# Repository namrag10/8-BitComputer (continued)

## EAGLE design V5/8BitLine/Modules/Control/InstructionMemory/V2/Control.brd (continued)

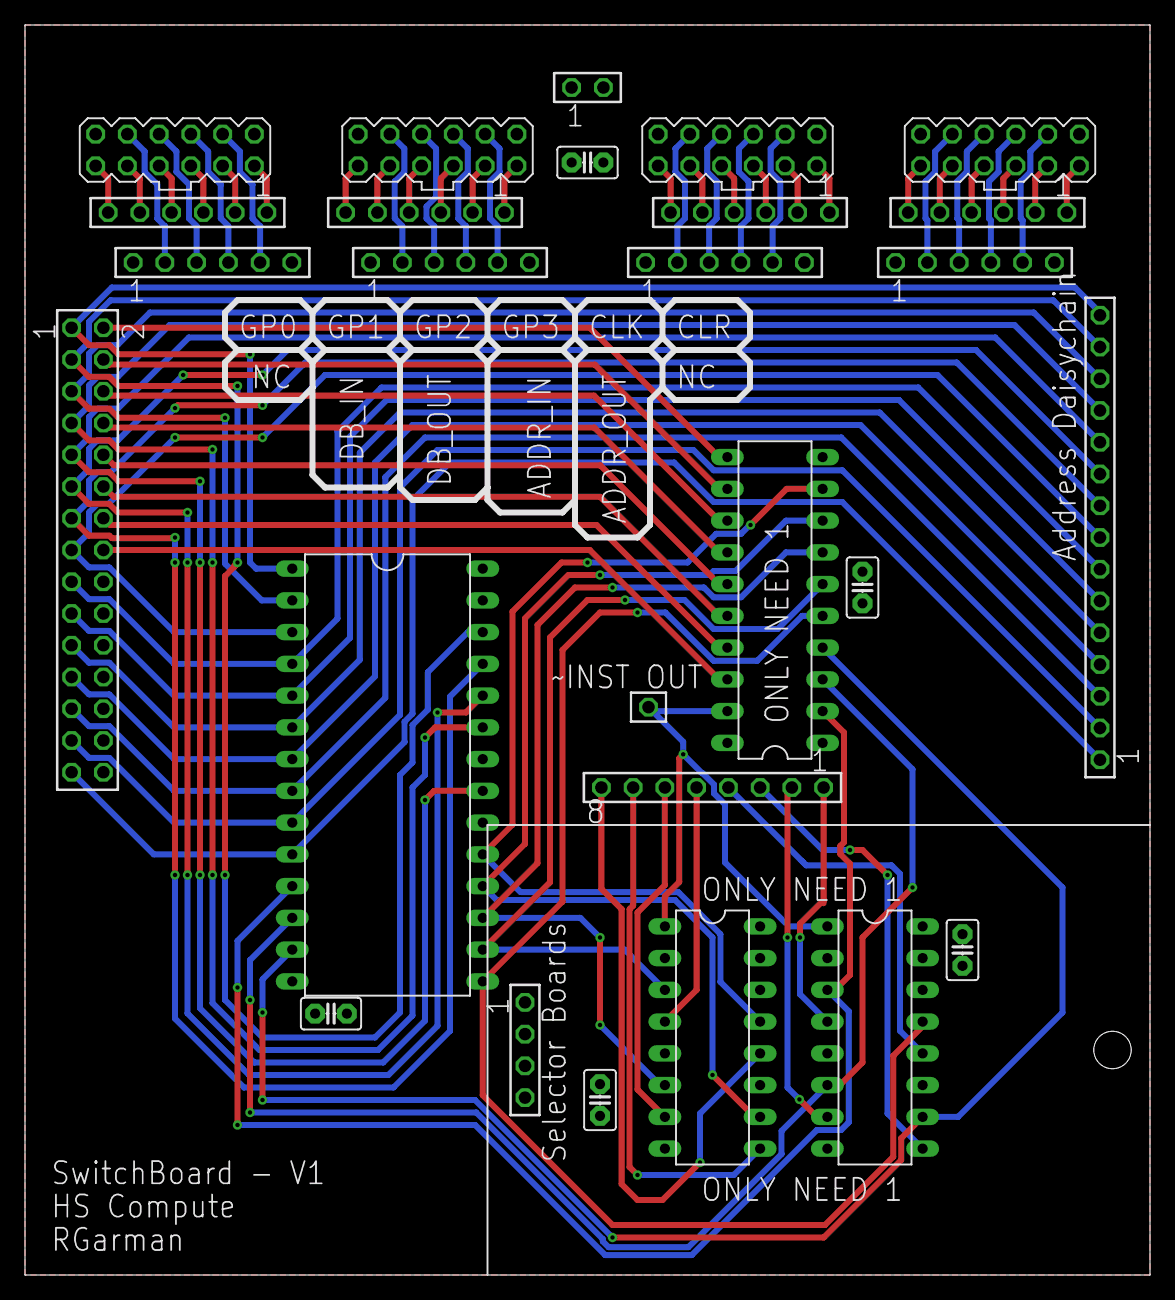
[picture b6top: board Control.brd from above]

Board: 2 copper layers, 90.0 x 100.0 mm, 27 parts (0 on the bottom side), 82 nets.

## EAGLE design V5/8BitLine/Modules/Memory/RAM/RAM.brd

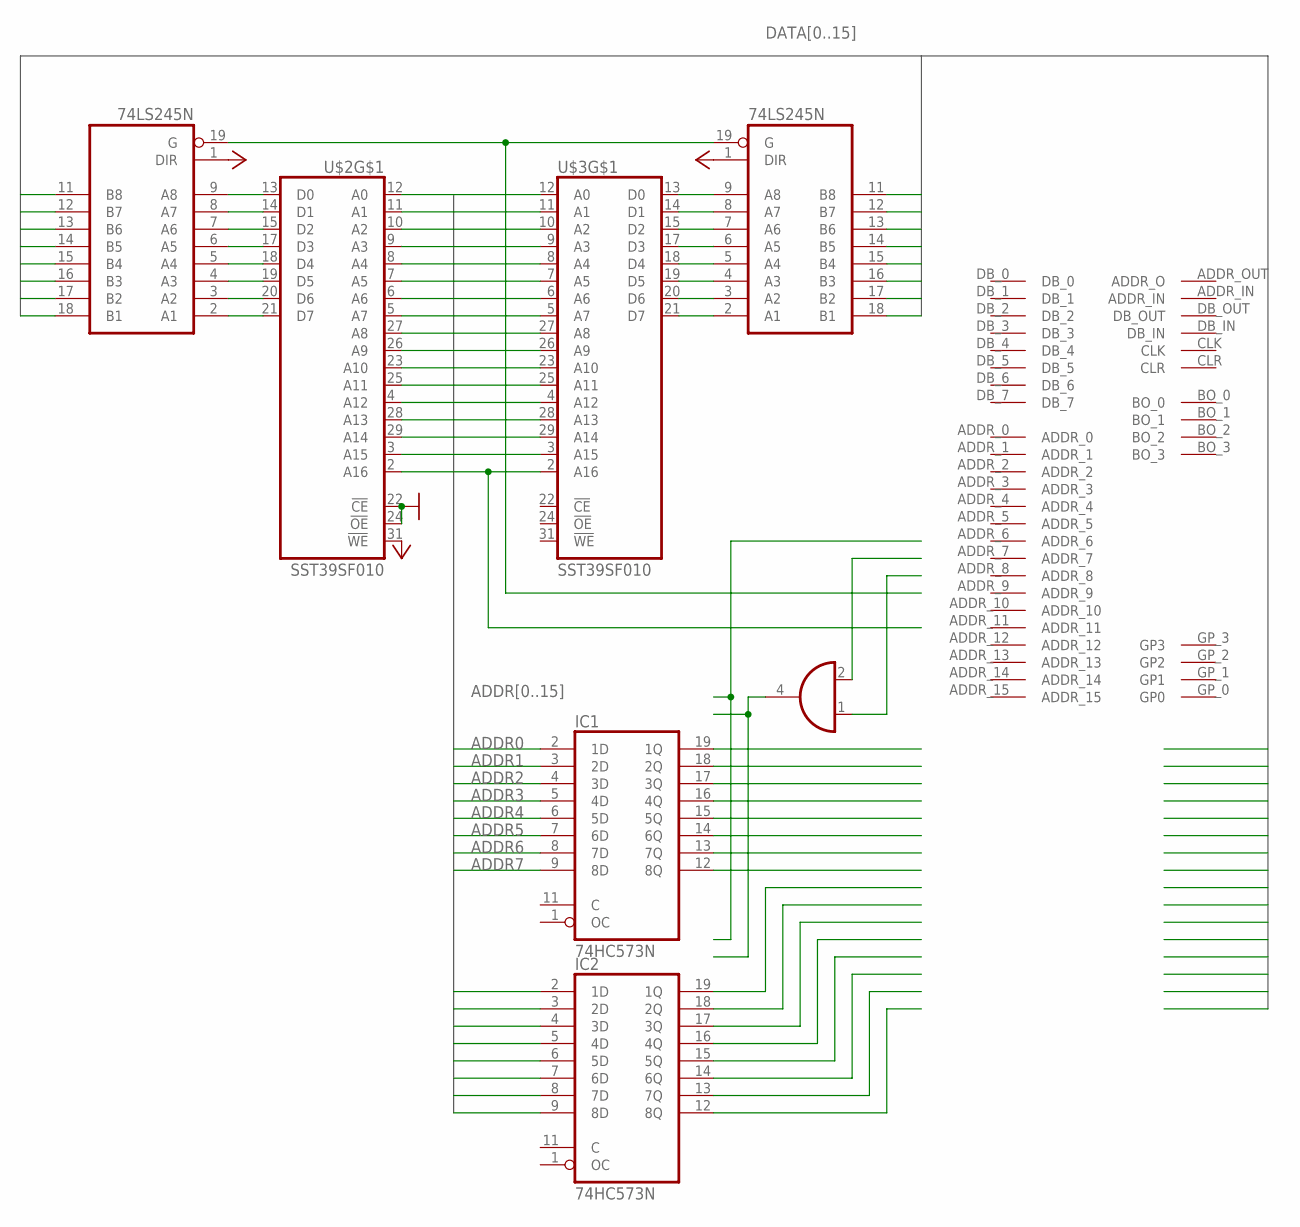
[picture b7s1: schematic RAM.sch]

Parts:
IC1, IC2: 74HC573N; DIL20
IC4: 74AHC1G08DCK; SC70-5
OUTPUT_BUFFER_MEMORY, OUTPUT_BUFFER_MEMORY1: 74LS245N; DIL20
U$1: BACKPLATE_INTERFACEEDGE_FINGER; BACK_INTERFACE-FOOT
U$2, U$3: SST39SF010; DIP32-WIDE

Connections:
ADDR0: IC1.2 (1D), U$2.12 (A0), U$3.12 (A0)
ADDR1: IC1.3 (2D), U$2.11 (A1), U$3.11 (A1)
ADDR2: IC1.4 (3D), U$2.10 (A2), U$3.10 (A2)
ADDR3: IC1.5 (4D), U$2.9 (A3), U$3.9 (A3)
ADDR4: IC1.6 (5D), U$2.8 (A4), U$3.8 (A4)
ADDR5: IC1.7 (6D), U$2.7 (A5), U$3.7 (A5)
ADDR6: IC1.8 (7D), U$2.6 (A6), U$3.6 (A6)
ADDR7: IC1.9 (8D), U$2.5 (A7), U$3.5 (A7)
ADDR8: IC2.2 (1D), U$2.27 (A8), U$3.27 (A8)
ADDR9: IC2.3 (2D), U$2.26 (A9), U$3.26 (A9)
ADDR10: IC2.4 (3D), U$2.23 (A10), U$3.23 (A10)
ADDR11: IC2.5 (4D), U$2.25 (A11), U$3.25 (A11)
ADDR12: IC2.6 (5D), U$2.4 (A12), U$3.4 (A12)
ADDR13: IC2.7 (6D), U$2.28 (A13), U$3.28 (A13)
ADDR14: IC2.8 (7D), U$2.3 (A15), U$2.29 (A14), U$3.29 (A14)
ADDR15: IC2.9 (8D), U$3.3 (A15)
DATA0: OUTPUT_BUFFER_MEMORY.11 (B8)
DATA1: OUTPUT_BUFFER_MEMORY.12 (B7)
DATA2: OUTPUT_BUFFER_MEMORY.13 (B6)
DATA3: OUTPUT_BUFFER_MEMORY.14 (B5)
DATA4: OUTPUT_BUFFER_MEMORY.15 (B4)
DATA5: OUTPUT_BUFFER_MEMORY.16 (B3)
DATA6: OUTPUT_BUFFER_MEMORY.17 (B2)
DATA7: OUTPUT_BUFFER_MEMORY.18 (B1)
DATA8: OUTPUT_BUFFER_MEMORY1.11 (B8)
DATA9: OUTPUT_BUFFER_MEMORY1.12 (B7)
DATA10: OUTPUT_BUFFER_MEMORY1.13 (B6)
DATA11: OUTPUT_BUFFER_MEMORY1.14 (B5)
DATA12: OUTPUT_BUFFER_MEMORY1.15 (B4)
DATA13: OUTPUT_BUFFER_MEMORY1.16 (B3)
DATA14: OUTPUT_BUFFER_MEMORY1.17 (B2)
DATA15: OUTPUT_BUFFER_MEMORY1.18 (B1)
GND: IC1.10 (GND), IC2.10 (GND), IC4.3 (GND), OUTPUT_BUFFER_MEMORY.10 (GND), OUTPUT_BUFFER_MEMORY1.10 (GND), U$1.GND_0 (GND), U$1.GND_1 (GND), U$2.16 (GND), U$2.22 (!CE), U$2.24 (!OE), U$3.16 (GND)
unnamed: U$2.2 (A16), U$3.2 (A16)
unnamed: OUTPUT_BUFFER_MEMORY.19 (G), OUTPUT_BUFFER_MEMORY1.19 (G)
unnamed: OUTPUT_BUFFER_MEMORY.2 (A1), U$2.21 (D7)
unnamed: OUTPUT_BUFFER_MEMORY.3 (A2), U$2.20 (D6)
unnamed: OUTPUT_BUFFER_MEMORY.4 (A3), U$2.19 (D5)
unnamed: OUTPUT_BUFFER_MEMORY.5 (A4), U$2.18 (D4)
unnamed: OUTPUT_BUFFER_MEMORY.6 (A5), U$2.17 (D3)
unnamed: OUTPUT_BUFFER_MEMORY.7 (A6), U$2.15 (D2)
unnamed: OUTPUT_BUFFER_MEMORY.8 (A7), U$2.14 (D1)
unnamed: OUTPUT_BUFFER_MEMORY.9 (A8), U$2.13 (D0)
unnamed: OUTPUT_BUFFER_MEMORY1.2 (A1), U$3.21 (D7)
unnamed: OUTPUT_BUFFER_MEMORY1.3 (A2), U$3.20 (D6)
unnamed: OUTPUT_BUFFER_MEMORY1.4 (A3), U$3.19 (D5)
unnamed: OUTPUT_BUFFER_MEMORY1.5 (A4), U$3.18 (D4)
unnamed: OUTPUT_BUFFER_MEMORY1.6 (A5), U$3.17 (D3)
unnamed: OUTPUT_BUFFER_MEMORY1.7 (A6), U$3.15 (D2)
unnamed: OUTPUT_BUFFER_MEMORY1.8 (A7), U$3.14 (D1)
unnamed: OUTPUT_BUFFER_MEMORY1.9 (A8), U$3.13 (D0)
VCC: IC1.20 (VCC), IC2.20 (VCC), IC4.5 (VCC), OUTPUT_BUFFER_MEMORY.1 (DIR), OUTPUT_BUFFER_MEMORY.20 (VCC), OUTPUT_BUFFER_MEMORY1.1 (DIR), OUTPUT_BUFFER_MEMORY1.20 (VCC), U$1.VCC_0 (VCC), U$1.VCC_1 (VCC), U$2.31 (!WE), U$2.32 (VCC), U$3.32 (VCC)

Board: 2 copper layers, 8 parts (0 on the bottom side), 36 nets, no tracks yet.
